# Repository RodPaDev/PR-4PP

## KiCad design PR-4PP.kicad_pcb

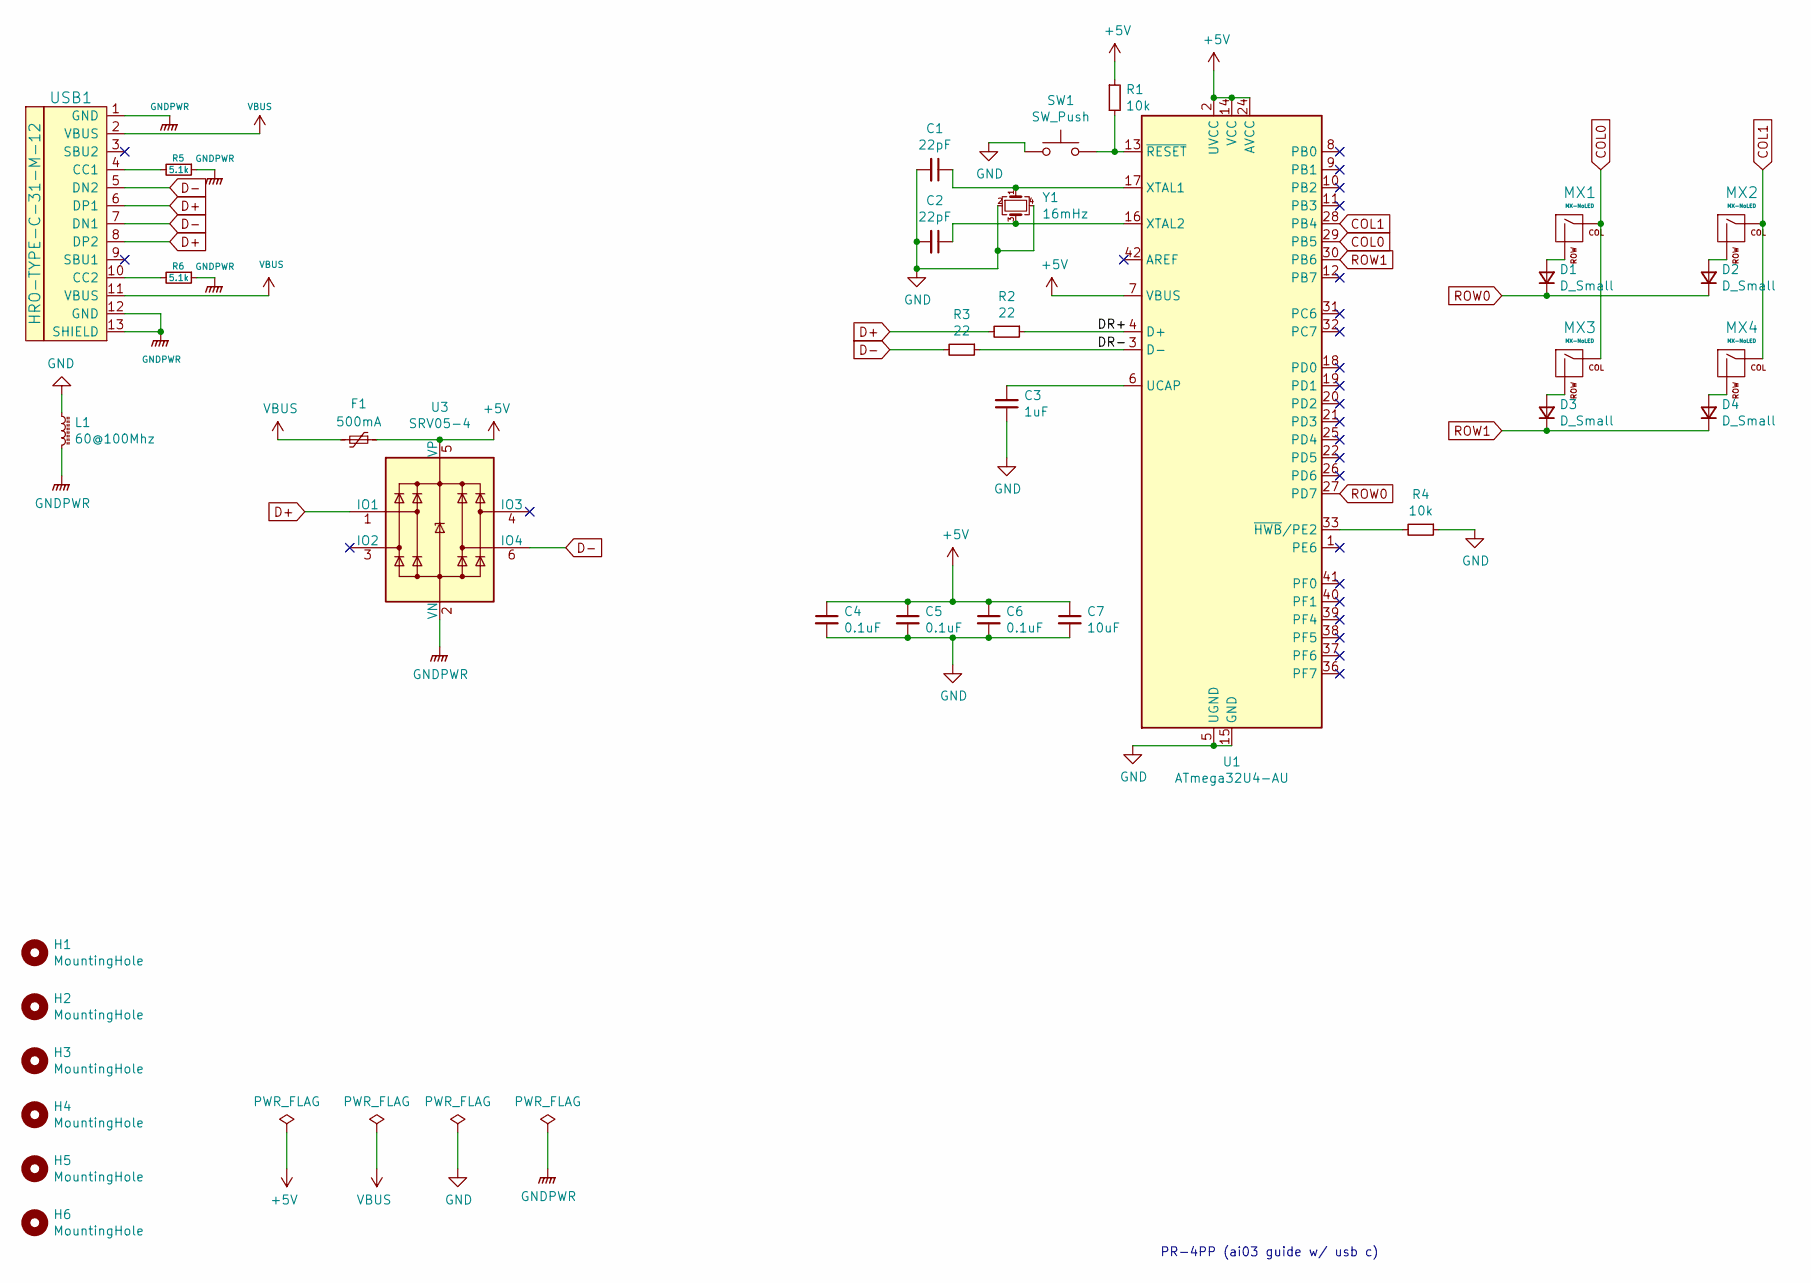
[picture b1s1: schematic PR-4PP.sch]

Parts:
C1, C2: 22pF; C_0805_2012Metric; LCSC C1804
C3: 1uF; C_0805_2012Metric; LCSC C28323
C4, C5, C6: 0.1uF; C_0805_2012Metric; LCSC C49678
C7: 10uF; C_0805_2012Metric; LCSC C15850
D1, D2, D3, D4: D_Small; D_SOD-123-Pretty; LCSC C64898
F1: 500mA; Fuse_1206_3216Metric_Pad1.42x1.75mm_HandSolder; LCSC C151162
H1, H2, H3, H4, H5, H6: MountingHole; MountingHole_2mm
L1: 60@100Mhz; L_1206_3216Metric_Pad1.42x1.75mm_HandSolder; LCSC C1017
MX1, MX2, MX3, MX4: MX-NoLED; MXOnly-1U-Hotswap-Antishear
R1: 10k; R_0805_2012Metric; LCSC C25804
R2, R3: 22; R_0805_2012Metric; LCSC C17561
R4: 10k; R_0805_2012Metric; LCSC C17414
R5, R6: 5.1k; C_0805_2012Metric_Pad1.15x1.40mm_HandSolder; LCSC C23186
SW1: SW_Push; SKQG-1155865; LCSC C318884
U1: ATmega32U4-AU; TQFP-44_10x10mm_P0.8mm; LCSC C44854
U3: SRV05-4; SOT-23-6; LCSC C85364
USB1: HRO-TYPE-C-31-M-12; HRO-TYPE-C-31-M-12-HandSoldering; LCSC C165948
Y1: 16mHz; Crystal_SMD_3225-4Pin_3.2x2.5mm; LCSC C13738

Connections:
+5V: C4.1, C5.1, C6.1, C7.1, F1.1, R1.1, U1.2 (UVCC), U1.7 (VBUS), U1.14 (VCC), U1.24 (AVCC), U1.34 (VCC), U1.44 (AVCC), U3.5 (VP)
/DR+: R2.1, U1.4 (D+)
/DR-: R3.1, U1.3 (D-)
COL0: MX1.1 (COL), MX3.1 (COL), U1.29 (PB5)
COL1: MX2.1 (COL), MX4.1 (COL), U1.28 (PB4)
D+: R2.2, U3.1 (IO1), USB1.6 (DP1), USB1.8 (DP2)
D-: R3.2, U3.6 (IO4), USB1.5 (DN2), USB1.7 (DN1)
GND: C1.2, C2.2, C3.1, C4.2, C5.2, C6.2, C7.2, L1.1, R4.1, SW1.1, U1.5 (UGND), U1.15 (GND), U1.23 (GND), U1.35 (GND), U1.43 (GND), Y1.2, Y1.4
GNDPWR: L1.2, R5.1, R6.1, U3.2 (VN), USB1.1 (GND), USB1.12 (GND), USB1.13 (SHIELD)
unnamed: C1.1, U1.17 (XTAL1), Y1.1
unnamed: C2.1, U1.16 (XTAL2), Y1.3
unnamed: C3.2, U1.6 (UCAP)
unnamed: D1.2 (A), MX1.2 (ROW)
unnamed: D2.2 (A), MX2.2 (ROW)
unnamed: D3.2 (A), MX3.2 (ROW)
unnamed: D4.2 (A), MX4.2 (ROW)
unnamed: R1.2, SW1.2, U1.13 (~RESET)
unnamed: R4.2, U1.33 (~HWB~/PE2)
unnamed: R5.2, USB1.4 (CC1)
unnamed: R6.2, USB1.10 (CC2)
ROW0: D1.1 (K), D2.1 (K), U1.27 (PD7)
ROW1: D3.1 (K), D4.1 (K), U1.30 (PB6)
VBUS: F1.2, USB1.2 (VBUS), USB1.11 (VBUS)

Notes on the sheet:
PR-4PP (ai03 guide w/ usb c)

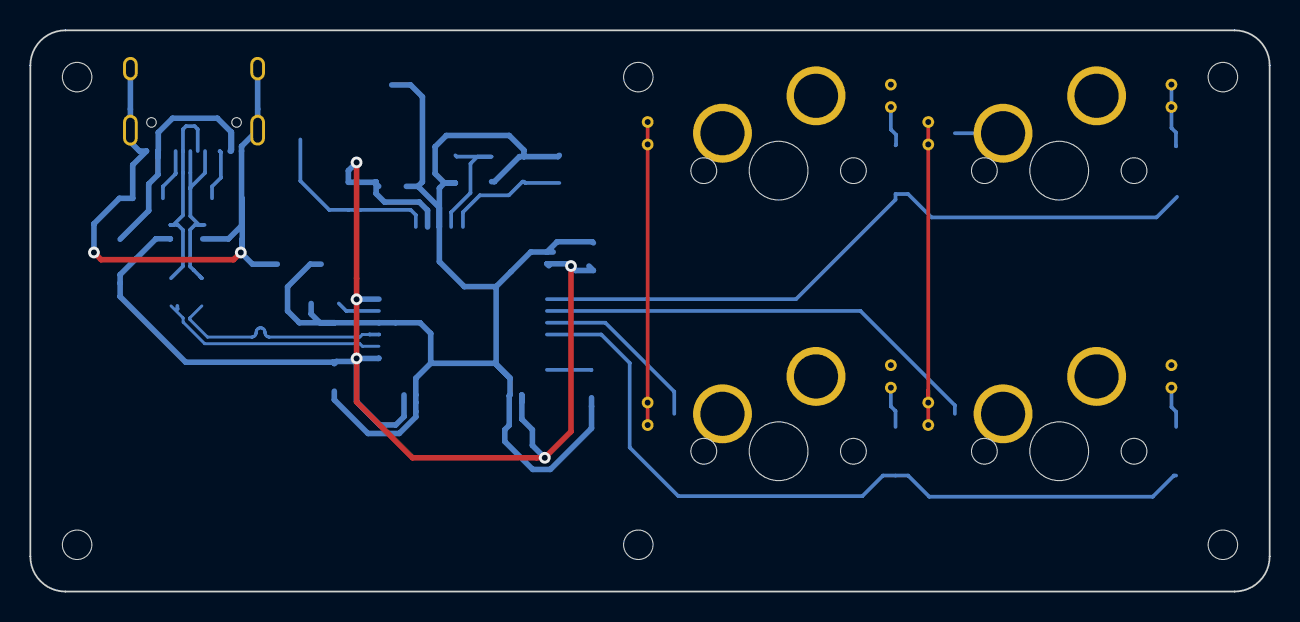
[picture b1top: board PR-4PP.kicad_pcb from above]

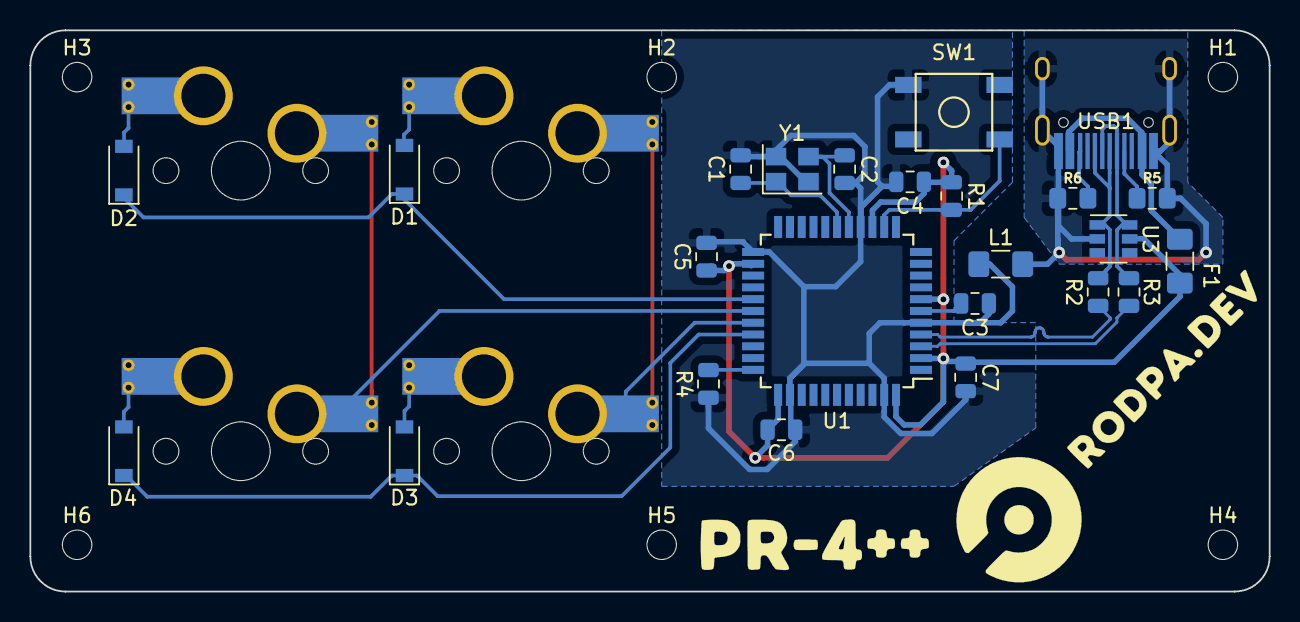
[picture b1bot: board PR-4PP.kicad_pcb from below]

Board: 2 copper layers, 84.1 x 38.1 mm, 36 parts (32 on the bottom side), 23 nets.

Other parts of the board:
Brand: rodpa.dev; rodpadev_logo_40x40mm
Model: PR-4++; PR-4PP_20x20mm

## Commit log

2021-10-13 add submodules
2021-10-13 add footprint libraries
2021-10-13 create schematic for MCU
2021-10-15 sch & pcb changes
2021-10-15 finish pcb
2021-10-16 route & create gerbers
2021-10-16 update gitignore
2021-10-16 bring decoupling closer
2021-10-16 move caps closer
2021-10-16 replace usb-mini-b with usb-c 2.0
2021-10-16 add reference
2021-10-16 replace esd for srv05-4 & add power flags
2021-10-16 make power flags obvious
2021-10-16 add footprints
2021-10-16 add submodule & implement new footprint
2021-10-17 reroute usb
2021-10-18 retrace differential data lines
2021-10-18 reroute & fillzones
2021-10-18 save project
2021-10-19 add silkscreen and part numbers
2021-10-19 add gerbers to gitignore
2021-10-19 add bom to gitignore
2021-10-19 add license
2021-10-19 small changes
2021-10-19 update backup
2021-10-19 migrate to kicad v5
2021-10-19 rearrange schema
2021-10-19 add gitignore
2021-10-19 remove files
